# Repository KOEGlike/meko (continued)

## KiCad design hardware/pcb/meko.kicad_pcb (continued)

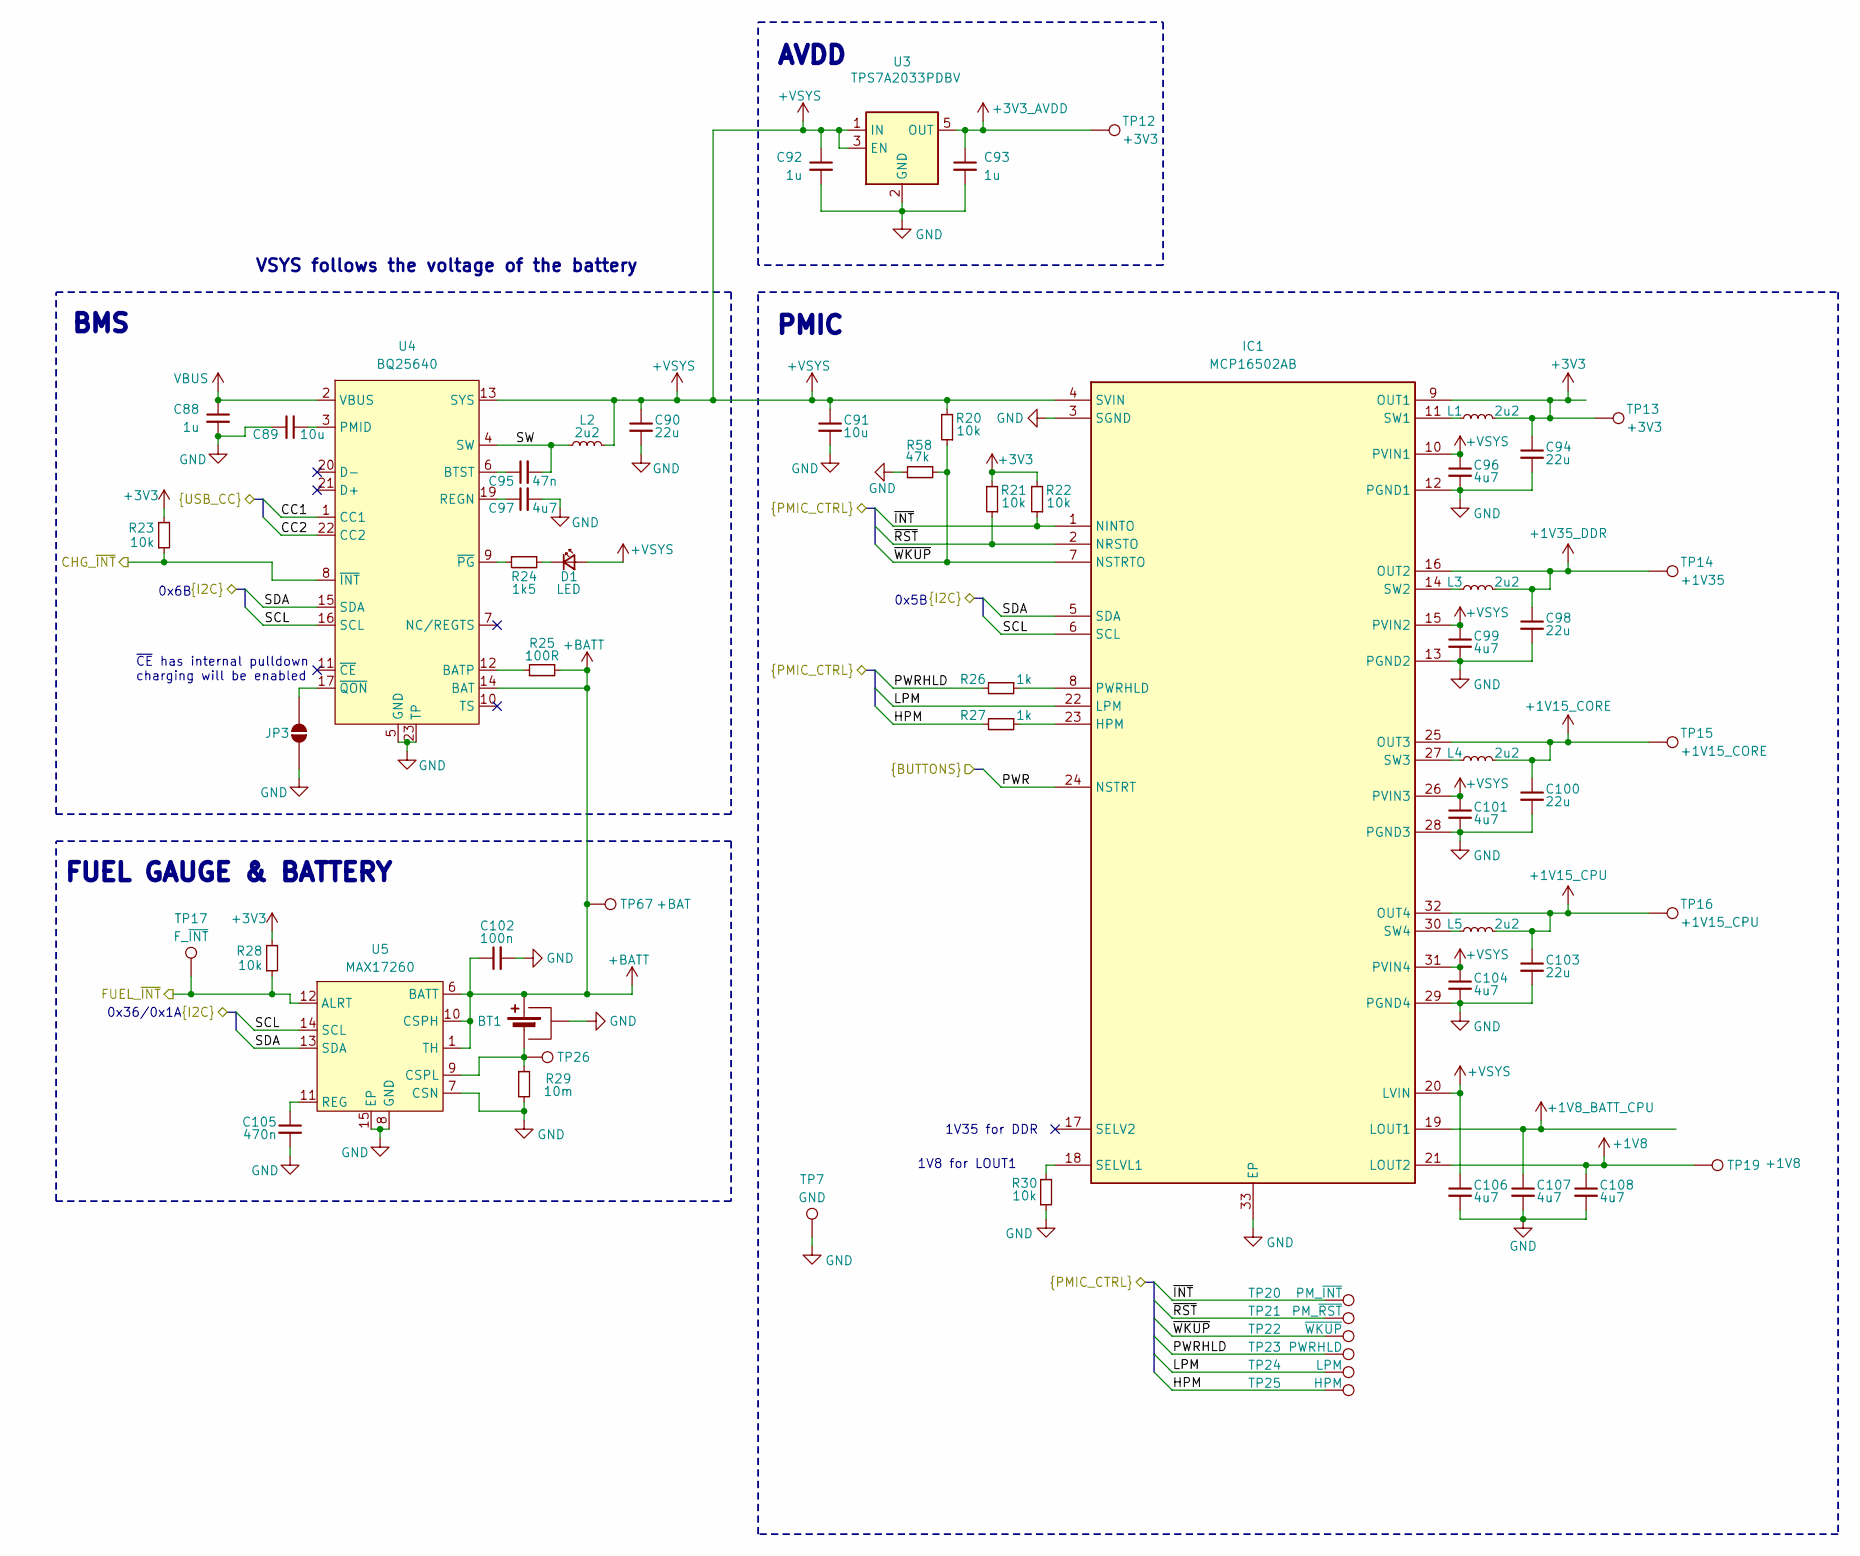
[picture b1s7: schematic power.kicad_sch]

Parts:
BT1: Battery_Cell; JST_GH_SM02B-GHS-TB_1x02-1MP_P1.25mm_Horizontal; MPN SM02B-GHS-TB(LF)(SN); LCSC C189893
C88, C92, C93: 1u; C_0402_1005Metric
C89, C91: 10u; C_0402_1005Metric
C90, C94, C98, C100, C103: 22u; C_0603_1608Metric
C95: 47n; C_0201_0603Metric
C96, C97, C99, C101, C104, C106, C107, C108: 4u7; C_0402_1005Metric
C102: 100n; C_0201_0603Metric
C105: 470n; C_0201_0603Metric
D1: LED; LED_0603_1608Metric; LCSC C965808
IC1: MCP16502AB; VQFN-32-1EP_5x5mm_P0.5mm_EP3.15x3.15mm; MPN MCP16502AB
JP3: SolderJumper_2_Open; SolderJumper-2_P1.3mm_Open_RoundedPad1.0x1.5mm
L1, L2, L3, L4, L5: 2u2; L_1008_2520Metric; LCSC C391305
R20: 10k; R_0201_0603Metric
R21, R22, R23, R28, R30: 10k; R_0402_1005Metric
R24: 1k5; R_0402_1005Metric
R25: 100R; R_0402_1005Metric
R26, R27: 1k; R_0402_1005Metric
R29: 10m; R_0402_1005Metric
R58: 47k; R_0402_1005Metric
TP7: GND; TestPoint_Pad_D1.0mm
TP12, TP13: +3V3; TestPoint_Pad_D1.0mm
TP14: +1V35; TestPoint_Pad_D1.0mm
TP15: +1V15_CORE; TestPoint_Pad_D1.0mm
TP16: +1V15_CPU; TestPoint_Pad_D1.0mm
TP17: F_~{INT}; TestPoint_Pad_D1.0mm
TP19: +1V8; TestPoint_Pad_D1.0mm
TP20: PM_~{INT}; TestPoint_Pad_D1.0mm
TP21: PM_~{RST}; TestPoint_Pad_D1.0mm
TP22: ~{WKUP}; TestPoint_Pad_D1.0mm
TP23: PWRHLD; TestPoint_Pad_D1.0mm
TP24: LPM; TestPoint_Pad_D1.0mm
TP25, TP26: HPM; TestPoint_Pad_D1.0mm
TP67: +BAT; TestPoint_Pad_D1.0mm
U3: TPS7A2033PDBV; SOT-23-5
U4: BQ25640; VDL0023A-MFG
U5: MAX17260; TDFN-14-1EP_3x3mm_P0.4mm_EP1.78x2.35mm

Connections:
+1V8: C108.1, IC1.21 (LOUT2), TP19.1 (1_1); also elsewhere on the board
+1V8_BATT_CPU: C107.1, IC1.19 (LOUT1); also elsewhere on the board
+1V15_CORE: C100.1, IC1.25 (OUT3), L4.2, TP15.1 (1_1); also elsewhere on the board
+1V15_CPU: C103.1, IC1.32 (OUT4), L5.2, TP16.1 (1_1); also elsewhere on the board
+1V35_DDR: C98.1, IC1.16 (OUT2), L3.2, TP14.1 (1_1); also elsewhere on the board
+3V3: C94.1, IC1.9 (OUT1), L1.2, R21.2, R22.2, R23.2, R28.2, TP13.1 (1_1); also elsewhere on the board
+3V3_AVDD: C93.1, TP12.1 (1_1), U3.5 (OUT); also elsewhere on the board
+BATT: BT1.1 (+), C102.1, R25.2, TP67.1 (1_1), U4.14 (BAT), U5.1 (TH), U5.6 (BATT), U5.10 (CSPH)
+VSYS: C90.1, C91.1, C92.1, C96.1, C99.1, C101.1, C104.1, C106.1, D1.2 (A), IC1.4 (SVIN), IC1.10 (PVIN1), IC1.15 (PVIN2), IC1.20 (LVIN), IC1.26 (PVIN3), IC1.31 (PVIN4), L2.2, R20.2, U3.1 (IN), U3.3 (EN), U4.13 (SYS)
/Audio/SCL: IC1.6 (SCL), U4.16 (SCL), U5.14 (SCL); also elsewhere on the board
/Audio/SDA: IC1.5 (SDA), U4.15 (SDA), U5.13 (SDA); also elsewhere on the board
/Buttons/PWR: IC1.24 (NSTRT); also elsewhere on the board
/Power/CC1: U4.1 (CC1); also elsewhere on the board
/Power/CC2: U4.22 (CC2); also elsewhere on the board
/Power/CHG_~INT: R23.1, U4.8 (~INT); also elsewhere on the board
/Power/FUEL_~INT: R28.1, TP17.1 (1_1), U5.12 (ALRT); also elsewhere on the board
/Power/HPM: R27.2, TP25.1 (1_1); also elsewhere on the board
/Power/LPM: IC1.22 (LPM), TP24.1 (1_1); also elsewhere on the board
/Power/PWRHLD: R26.2, TP23.1 (1_1); also elsewhere on the board
/Power/SW: C95.2, L2.1, U4.4 (SW)
/Power/~INT: IC1.1 (NINTO), R22.1, TP20.1 (1_1); also elsewhere on the board
/Power/~RST: IC1.2 (NRSTO), R21.1, TP21.1 (1_1); also elsewhere on the board
/Power/~WKUP: IC1.7 (NSTRTO), R20.1, R58.2, TP22.1 (1_1); also elsewhere on the board
GND: BT1.MP, C88.2, C89.2, C90.2, C91.2, C92.2, C93.2, C94.2, C96.2, C97.2, C98.2, C99.2, C100.2, C101.2, C102.2, C103.2, C104.2, C105.2, C106.2, C107.2, C108.2, IC1.3 (SGND), IC1.12 (PGND1), IC1.13 (PGND2), IC1.28 (PGND3), IC1.29 (PGND4), IC1.33 (EP), JP3.1 (A), R29.2, R30.1, R58.1, TP7.1 (1_1), U3.2 (GND), U4.5 (GND), U4.18 (GND), U4.23 (TP), U5.7 (CSN), U5.8 (GND), U5.15 (EP); also elsewhere on the board
unnamed: BT1.2 (-), R29.1, TP26.1 (1_1), U5.9 (CSPL)
unnamed: D1.1 (K), R24.2
unnamed: IC1.23 (HPM), R27.1
unnamed: IC1.8 (PWRHLD), R26.1
unnamed: IC1.18 (SELVL1), R30.2
unnamed: IC1.11 (SW1), L1.1
unnamed: IC1.14 (SW2), L3.1
unnamed: IC1.27 (SW3), L4.1
unnamed: IC1.30 (SW4), L5.1
unnamed: JP3.2 (B), U4.17 (~QON)
unnamed: R25.1, U4.12 (BATP)
unnamed: C95.1, U4.6 (BTST)
unnamed: C89.1, U4.3 (PMID)
unnamed: C97.1, U4.19 (REGN)
unnamed: R24.1, U4.9 (~PG)
unnamed: C105.1, U5.11 (REG)
VBUS: C88.1, U4.2 (VBUS); also elsewhere on the board

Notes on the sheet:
0x5B
0x6B
VSYS follows the voltage of the battery
0x36/0x1A
1V35 for DDR
PMIC
BMS
AVDD
1V8 for LOUT1
~{CE} has internal pulldown charging will be enabled
FUEL GAUGE & BATTERY

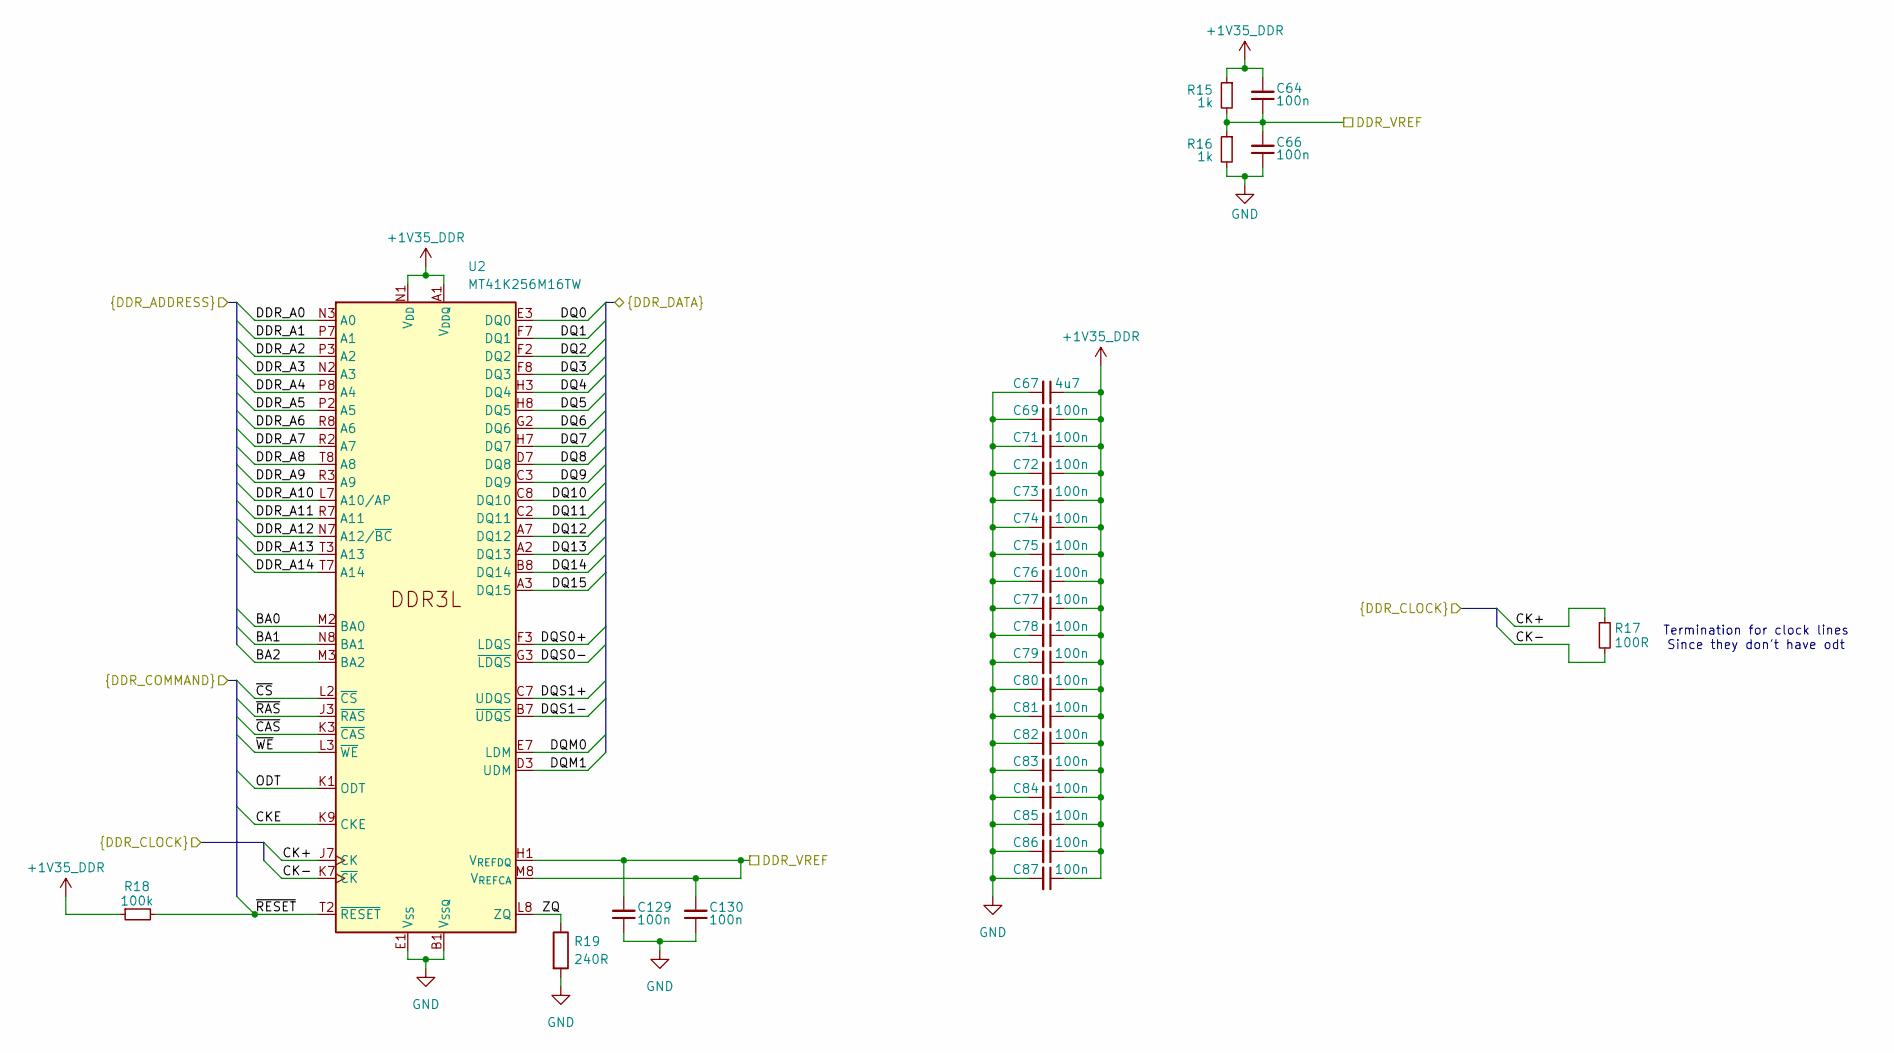
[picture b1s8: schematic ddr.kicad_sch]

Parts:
C64, C66, C69, C71, C72, C73, C74, C76, C77, C78, C79, C80, C81, C82, C83, C84, C85, C86, C87, C129, C130: 100n; C_0201_0603Metric
C67: 4u7; C_0402_1005Metric
C75: 100n; C_0201_0603Metric_Dense
R15, R16: 1k; R_0201_0603Metric
R17: 100R; R_0201_0603Metric
R18: 100k; R_0201_0603Metric
R19: 240R; R_0201_0603Metric
U2: MT41K256M16TW; Micron_FBGA-96_8x14mm_Layout9x16_P0.8mm; LCSC C253882

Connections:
+1V35_DDR: C64.2, C67.1, C69.1, C71.1, C72.1, C73.1, C74.1, C75.1, C76.1, C77.1, C78.1, C79.1, C80.1, C81.1, C82.1, C83.1, C84.1, C85.1, C86.1, C87.1, R15.1, R18.1, U2.A1 (V_{DDQ}), U2.A8 (V_{DDQ}), U2.B2 (V_{DD}), U2.C1 (V_{DDQ}), U2.C9 (V_{DDQ}), U2.D2 (V_{DDQ}), U2.D9 (V_{DD}), U2.E9 (V_{DDQ}), U2.F1 (V_{DDQ}), U2.G7 (V_{DD}), U2.H2 (V_{DDQ}), U2.H9 (V_{DDQ}), U2.K2 (V_{DD}), U2.K8 (V_{DD}), U2.N1 (V_{DD}), U2.N9 (V_{DD}), U2.R1 (V_{DD}), U2.R9 (V_{DD}); also elsewhere on the board
/DDR/BA0: U2.M2 (BA0); also elsewhere on the board
/DDR/BA1: U2.N8 (BA1); also elsewhere on the board
/DDR/BA2: U2.M3 (BA2); also elsewhere on the board
/DDR/CK+: R17.1, U2.J7 (CK); also elsewhere on the board
/DDR/CK-: R17.2, U2.K7 (~CK); also elsewhere on the board
/DDR/CKE: U2.K9 (CKE); also elsewhere on the board
/DDR/DDR_A0: U2.N3 (A0); also elsewhere on the board
/DDR/DDR_A1: U2.P7 (A1); also elsewhere on the board
/DDR/DDR_A2: U2.P3 (A2); also elsewhere on the board
/DDR/DDR_A3: U2.N2 (A3); also elsewhere on the board
/DDR/DDR_A4: U2.P8 (A4); also elsewhere on the board
/DDR/DDR_A5: U2.P2 (A5); also elsewhere on the board
/DDR/DDR_A6: U2.R8 (A6); also elsewhere on the board
/DDR/DDR_A7: U2.R2 (A7); also elsewhere on the board
/DDR/DDR_A8: U2.T8 (A8); also elsewhere on the board
/DDR/DDR_A9: U2.R3 (A9); also elsewhere on the board
/DDR/DDR_A10: U2.L7 (A10/AP); also elsewhere on the board
/DDR/DDR_A11: U2.R7 (A11); also elsewhere on the board
/DDR/DDR_A12: U2.N7 (A12/~BC); also elsewhere on the board
/DDR/DDR_A13: U2.T3 (A13); also elsewhere on the board
/DDR/DDR_A14: U2.T7 (A14); also elsewhere on the board
/DDR/DDR_VREF: C64.1, C66.2, C129.2, C130.2, R15.2, R16.1, U2.H1 (V_{REFDQ}), U2.M8 (V_{REFCA}); also elsewhere on the board
/DDR/DQ0: U2.E3 (DQ0); also elsewhere on the board
/DDR/DQ1: U2.F7 (DQ1); also elsewhere on the board
/DDR/DQ2: U2.F2 (DQ2); also elsewhere on the board
/DDR/DQ3: U2.F8 (DQ3); also elsewhere on the board
/DDR/DQ4: U2.H3 (DQ4); also elsewhere on the board
/DDR/DQ5: U2.H8 (DQ5); also elsewhere on the board
/DDR/DQ6: U2.G2 (DQ6); also elsewhere on the board
/DDR/DQ7: U2.H7 (DQ7); also elsewhere on the board
/DDR/DQ8: U2.D7 (DQ8); also elsewhere on the board
/DDR/DQ9: U2.C3 (DQ9); also elsewhere on the board
/DDR/DQ10: U2.C8 (DQ10); also elsewhere on the board
/DDR/DQ11: U2.C2 (DQ11); also elsewhere on the board
/DDR/DQ12: U2.A7 (DQ12); also elsewhere on the board
/DDR/DQ13: U2.A2 (DQ13); also elsewhere on the board
/DDR/DQ14: U2.B8 (DQ14); also elsewhere on the board
/DDR/DQ15: U2.A3 (DQ15); also elsewhere on the board
/DDR/DQM0: U2.E7 (LDM); also elsewhere on the board
/DDR/DQM1: U2.D3 (UDM); also elsewhere on the board
/DDR/DQS0+: U2.F3 (LDQS); also elsewhere on the board
/DDR/DQS0-: U2.G3 (~LDQS); also elsewhere on the board
/DDR/DQS1+: U2.C7 (UDQS); also elsewhere on the board
/DDR/DQS1-: U2.B7 (~UDQS); also elsewhere on the board
/DDR/ODT: U2.K1 (ODT); also elsewhere on the board
/DDR/ZQ: R19.1, U2.L8 (ZQ)
/DDR/~CAS: U2.K3 (~CAS); also elsewhere on the board
/DDR/~CS: U2.L2 (~CS); also elsewhere on the board
/DDR/~RAS: U2.J3 (~RAS); also elsewhere on the board
/DDR/~RESET: R18.2, U2.T2 (~RESET); also elsewhere on the board
/DDR/~WE: U2.L3 (~WE); also elsewhere on the board
GND: C66.1, C67.2, C69.2, C71.2, C72.2, C73.2, C74.2, C75.2, C76.2, C77.2, C78.2, C79.2, C80.2, C81.2, C82.2, C83.2, C84.2, C85.2, C86.2, C87.2, C129.1, C130.1, R16.2, R19.2, U2.A9 (V_{SS}), U2.B1 (V_{SSQ}), U2.B3 (V_{SS}), U2.B9 (V_{SSQ}), U2.D1 (V_{SSQ}), U2.D8 (V_{SSQ}), U2.E1 (V_{SS}), U2.E2 (V_{SSQ}), U2.E8 (V_{SSQ}), U2.F9 (V_{SSQ}), U2.G1 (V_{SSQ}), U2.G8 (V_{SS}), U2.G9 (V_{SSQ}), U2.J2 (V_{SS}), U2.J8 (V_{SS}), U2.M1 (V_{SS}), U2.M9 (V_{SS}), U2.P1 (V_{SS}), U2.P9 (V_{SS}), U2.T1 (V_{SS}), U2.T9 (V_{SS}); also elsewhere on the board

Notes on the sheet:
Termination for clock lines Since they don't have odt

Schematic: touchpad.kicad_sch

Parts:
C124, C125: 1u; C_0402_1005Metric
J9: 503480-0540; MPN 5034800540; LCSC C5527934
R57: 10k; R_0402_1005Metric
TP62: T_~{INT}; TestPoint_Pad_D1.0mm
TP63: HAPT+; TestPoint_Pad_D2.0mm
TP64: HAPT-; TestPoint_Pad_D2.0mm
TP65: HAPT_EN; TestPoint_Pad_D1.0mm
U7: DRV2605LDGS; TSSOP-10_3x3mm_P0.5mm

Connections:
+3V3: C124.2, J9.1, R57.2, U7.6 (VDD/NC), U7.10 (VDD); also elsewhere on the board
/Audio/SCL: U7.2 (SCL); also elsewhere on the board
/Audio/SDA: U7.3 (SDA); also elsewhere on the board
/SAMA7/HAPT_EN: TP65.1 (1_1), U7.5 (EN); also elsewhere on the board
/SAMA7/TOUCH.SCL: J9.5; also elsewhere on the board
/SAMA7/TOUCH.SDA: J9.3; also elsewhere on the board
/SAMA7/TOUCH_~INT: J9.2, R57.1, TP62.1 (1_1); also elsewhere on the board
/Touchpad/HAPT+: TP63.1 (1_1), U7.7 (OUT+)
/Touchpad/HAPT-: TP64.1 (1_1), U7.9 (OUT-)
GND: C124.1, C125.1, J9.4, J9.MP_1, J9.MP_2, U7.4 (IN/TRIG), U7.8 (GND); also elsewhere on the board
unnamed: C125.2, U7.1 (REG)

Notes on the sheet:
TOUCHPAD CONN
HAPTIC

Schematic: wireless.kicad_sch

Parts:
C109, C110: 1u; C_0402_1005Metric
C111, C112: 9p; C_0201_0603Metric
IC2: MAYA-W386-00B; MPN MAYA-W383-00B
R31, R32, R38, R39: 10k; R_0402_1005Metric
R33, R34, R35, R36, R37: 47k; R_0402_1005Metric
TP28: BT_EN; TestPoint_Pad_D1.0mm
TP29: RF_RX; TestPoint_Pad_D1.0mm
TP30: RF_TX; TestPoint_Pad_D1.0mm
TP31: RF_~{CTS}; TestPoint_Pad_D1.0mm
TP32: RF_~{RTS}; TestPoint_Pad_D1.0mm
TP33: RF_MCLK; TestPoint_Pad_D1.0mm
TP34: RF_BCLK; TestPoint_Pad_D1.0mm
TP35: RF_FSYNC; TestPoint_Pad_D1.0mm
TP36: RF_DOUT; TestPoint_Pad_D1.0mm
TP37: RF_DIN; TestPoint_Pad_D1.0mm
TP40: WL_EN; TestPoint_Pad_D1.0mm
TP41: RF_CK; TestPoint_Pad_D1.0mm
TP42: RF_CMD; TestPoint_Pad_D1.0mm
TP43: RF_DAT0; TestPoint_Pad_D1.0mm
TP44: RF_DAT1; TestPoint_Pad_D1.0mm
TP45: RF_DAT2; TestPoint_Pad_D1.0mm
TP46: RF_DAT3; TestPoint_Pad_D1.0mm
Y3: 32kHz768; Crystal_SMD_MicroCrystal_CC7V-T1A-2Pin_3.2x1.5mm; MPN SC-32S32.768kHz20PPM7pF

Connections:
+1V8: C109.2, IC2.A2 (1V8); also elsewhere on the board
+3V3: C110.1, IC2.A7 (3V3), IC2.B7 (3V3), R33.1, R34.1, R35.1, R36.1, R37.1; also elsewhere on the board
/SAMA7/BT.BCLK: IC2.D8 (PCM_CLK), TP34.1 (1_1); also elsewhere on the board
/SAMA7/BT.DEV_WAKE: IC2.J9 (BT_DEV_WAKE), R31.2; also elsewhere on the board
/SAMA7/BT.DIN: IC2.E9 (PCM_DIN), TP37.1 (1_1); also elsewhere on the board
/SAMA7/BT.DOUT: IC2.F9 (PCM_DOUT), TP36.1 (1_1); also elsewhere on the board
/SAMA7/BT.EN: IC2.J7 (BT_EN), TP28.1 (1_1); also elsewhere on the board
/SAMA7/BT.FSYNC: IC2.F8 (PCM_SYNC), TP35.1 (1_1); also elsewhere on the board
/SAMA7/BT.HOST_WAKE: IC2.E7 (BT_HOST_WAKE), R32.2; also elsewhere on the board
/SAMA7/BT.MCLK: IC2.E8 (PCM_MCLK), TP33.1 (1_1); also elsewhere on the board
/SAMA7/BT.RX: IC2.G8 (UART_RX), TP29.1 (1_1); also elsewhere on the board
/SAMA7/BT.TX: IC2.G9 (UART_TX), TP30.1 (1_1); also elsewhere on the board
/SAMA7/BT.~CTS: IC2.H8 (UART_CTSN), TP31.1 (1_1); also elsewhere on the board
/SAMA7/BT.~RTS: IC2.H9 (UART_RTSN), TP32.1 (1_1); also elsewhere on the board
/SAMA7/WIFI.CK: IC2.A4 (SD_CLK), TP41.1 (1_1); also elsewhere on the board
/SAMA7/WIFI.CMD: IC2.B4 (SD_CMD), R33.2, TP42.1 (1_1); also elsewhere on the board
/SAMA7/WIFI.DAT0: IC2.B3 (SD_DAT[0]), R34.2, TP43.1 (1_1); also elsewhere on the board
/SAMA7/WIFI.DAT1: IC2.A3 (SD_DAT[1]), R35.2, TP44.1 (1_1); also elsewhere on the board
/SAMA7/WIFI.DAT2: IC2.B5 (SD_DAT[2]), R36.2, TP45.1 (1_1); also elsewhere on the board
/SAMA7/WIFI.DAT3: IC2.A5 (SD_DAT[3]), R37.2, TP46.1 (1_1); also elsewhere on the board
/SAMA7/WL.DEV_WAKE: IC2.J8 (WL_DEV_WAKE), R39.2; also elsewhere on the board
/SAMA7/WL.EN: IC2.J3 (WL_EN), TP40.1 (1_1); also elsewhere on the board
/SAMA7/WL.HOST_WAKE: IC2.F7 (WL_HOST_WAKE), R38.2; also elsewhere on the board
/Wireless/ANT: IC2.K9 (RF_ANT1), IC2.L9 (ANT_EXT_FEED)
GND: C109.1, C110.2, C111.2, C112.2, IC2.A1 (GND), IC2.A9 (GND), IC2.B2 (GND), IC2.B8 (GND), IC2.E4 (GND), IC2.E5 (GND), IC2.F4 (GND), IC2.F5 (GND), IC2.H4 (GND), IC2.H5 (GND), IC2.H7 (JTAG_SEL), IC2.K2 (GND), IC2.K3 (GND), IC2.K4 (GND), IC2.K5 (GND), IC2.K6 (GND), IC2.K7 (GND), IC2.K8 (GND), IC2.L1 (GND), IC2.M1 (GND), IC2.M2 (GND), IC2.M8 (GND), IC2.M9 (GND), R31.1, R32.1, R38.1, R39.1; also elsewhere on the board
unnamed: C112.1, IC2.C2 (SLP_XTAL_IN), Y3.1
unnamed: C111.1, IC2.D2 (SLP_XTAL_OUT), Y3.2

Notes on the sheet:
WL EN has internal pull down
Mic input, and digital outputs
RF Switch Control Lines
BT EN has internal pull down
External Memory/Flash
Connecting the output to the integrated PCB antenna
JTAG Pins

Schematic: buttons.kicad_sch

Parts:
C126: 100n; C_0201_0603Metric
R56: 10k; R_0402_1005Metric
SW1, SW2, SW3, SW4, SW5: SW_Push_Shielded; SW_Push_1P1T-MP_NO_Horizontal_Alps_SKRTLAE010; MPN SKRTLAE010; LCSC C110293

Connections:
/Buttons/PWR: C126.2, R56.2; also elsewhere on the board
/Buttons/SIDE_L: SW4.2; also elsewhere on the board
/Buttons/SIDE_R: SW5.2; also elsewhere on the board
/Buttons/VOL+: SW2.2; also elsewhere on the board
/Buttons/VOL-: SW3.2; also elsewhere on the board
GND: C126.1, SW1.1, SW1.MP (B), SW2.1, SW2.MP (B), SW3.1, SW3.MP (B), SW4.1, SW4.MP (B), SW5.1, SW5.MP (B); also elsewhere on the board
unnamed: R56.1, SW1.2

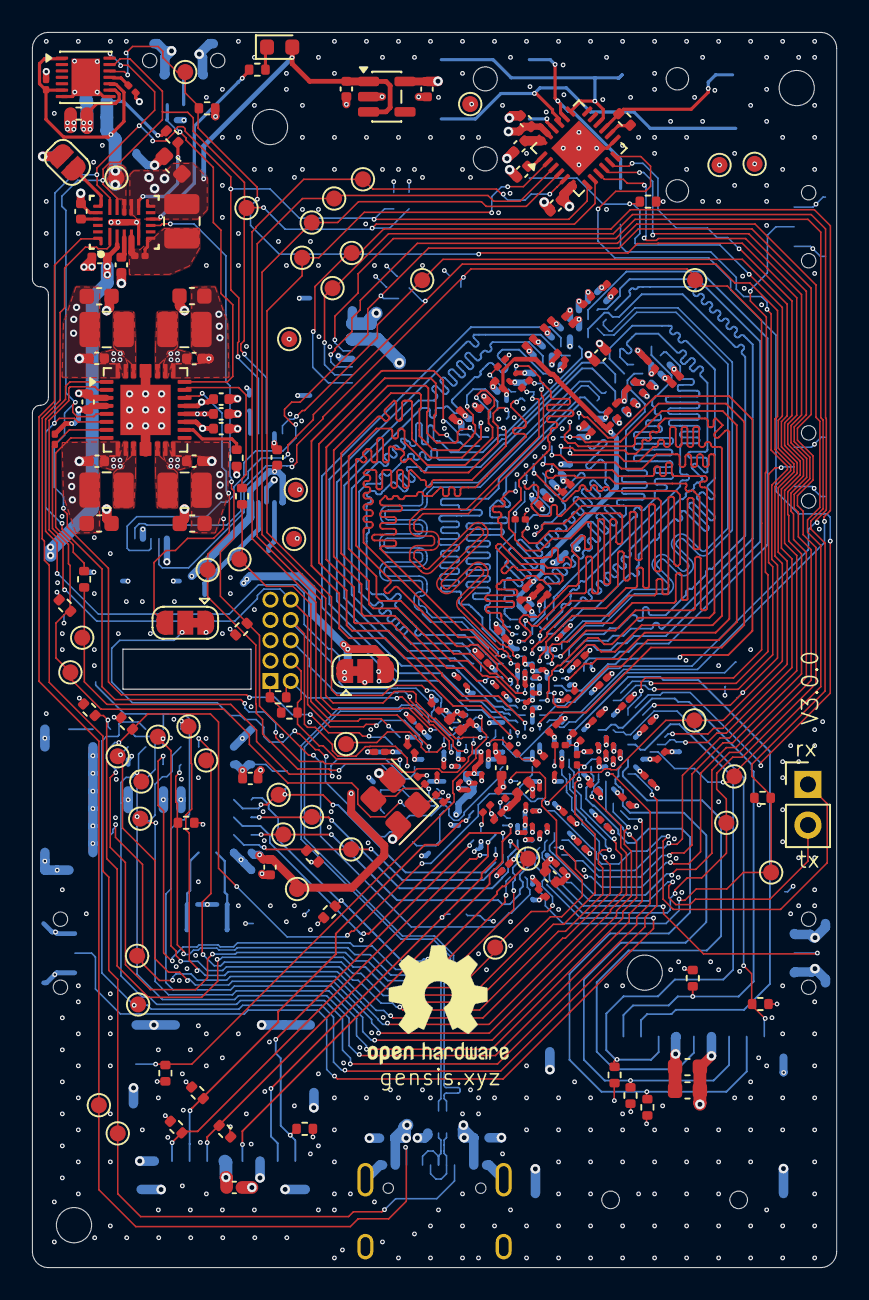
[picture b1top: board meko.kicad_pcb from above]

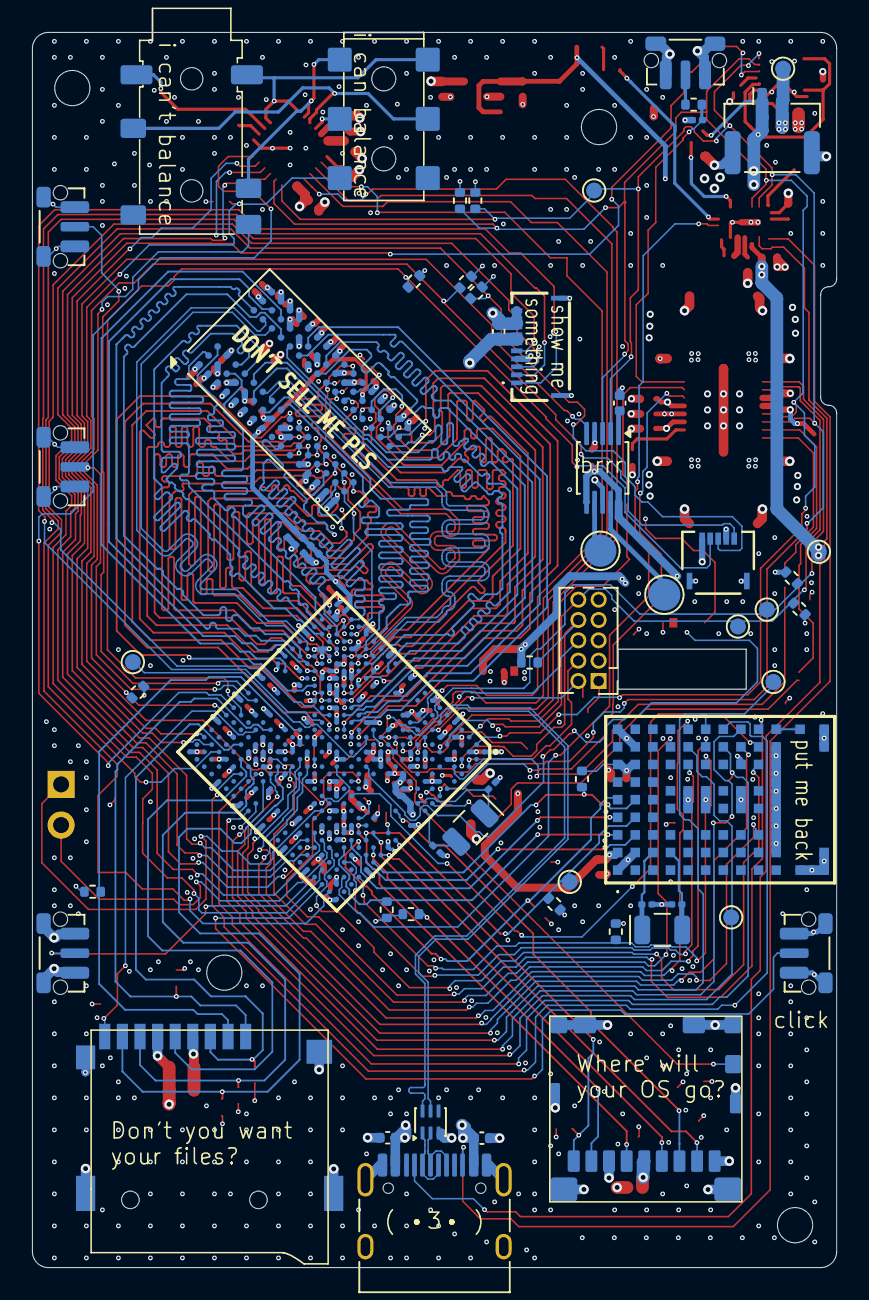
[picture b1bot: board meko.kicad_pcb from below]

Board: 6 copper layers, 50.2 x 77.2 mm, 275 parts (61 on the bottom side), 189 nets.

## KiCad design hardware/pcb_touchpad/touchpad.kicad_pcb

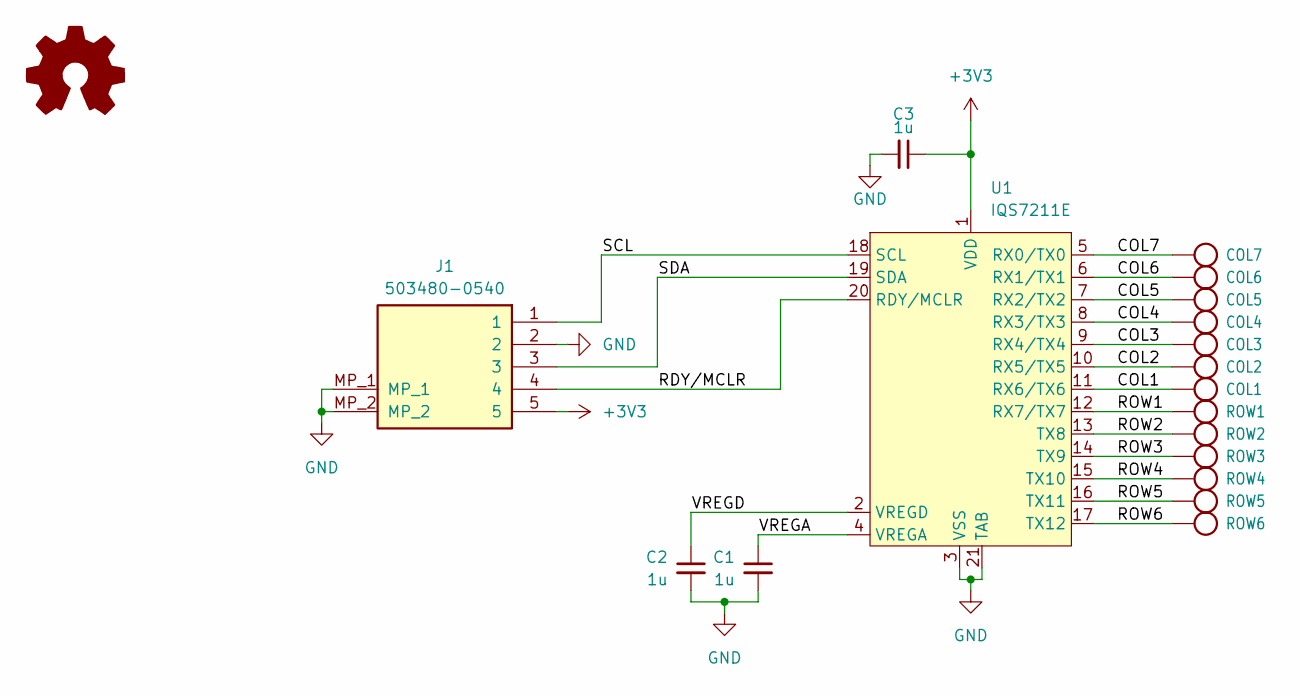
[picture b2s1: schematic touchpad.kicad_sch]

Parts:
C1, C2, C3: 1u; C_0402_1005Metric
COL1, COL2, COL3, COL4, COL5, COL6, COL7: TESTPOINTPAD_0_5MM; PAD_0_5MM
J1: 503480-0540; MPN 5034800540; LCSC C5527934
ROW1, ROW2, ROW3, ROW4, ROW5, ROW6: TESTPOINTPAD_0_5MM; PAD_0_5MM
SYM1: Logo_Open_Hardware_Small; OSHW-Logo2_14.6x12mm_SilkScreen
U1: IQS7211E; QFN-20-1EP_3x3mm_P0.4mm_EP1.65x1.65mm

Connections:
+3V3: C3.1, J1.5, U1.1 (VDD)
/COL1: COL1.P1 (P1_P1), U1.11 (RX6/TX6)
/COL2: COL2.P1 (P1_P1), U1.10 (RX5/TX5)
/COL3: COL3.P1 (P1_P1), U1.9 (RX4/TX4)
/COL4: COL4.P1 (P1_P1), U1.8 (RX3/TX3)
/COL5: COL5.P1 (P1_P1), U1.7 (RX2/TX2)
/COL6: COL6.P1 (P1_P1), U1.6 (RX1/TX1)
/COL7: COL7.P1 (P1_P1), U1.5 (RX0/TX0)
/RDY/MCLR: J1.4, U1.20 (RDY/MCLR)
/ROW1: ROW1.P1 (P1_P1), U1.12 (RX7/TX7)
/ROW2: ROW2.P1 (P1_P1), U1.13 (TX8)
/ROW3: ROW3.P1 (P1_P1), U1.14 (TX9)
/ROW4: ROW4.P1 (P1_P1), U1.15 (TX10)
/ROW5: ROW5.P1 (P1_P1), U1.16 (TX11)
/ROW6: ROW6.P1 (P1_P1), U1.17 (TX12)
/SCL: J1.1, U1.18 (SCL)
/SDA: J1.3, U1.19 (SDA)
/VREGA: C1.1, U1.4 (VREGA)
/VREGD: C2.1, U1.2 (VREGD)
GND: C1.2, C2.2, C3.2, J1.2, J1.MP_1, J1.MP_2, U1.3 (VSS), U1.21 (TAB)

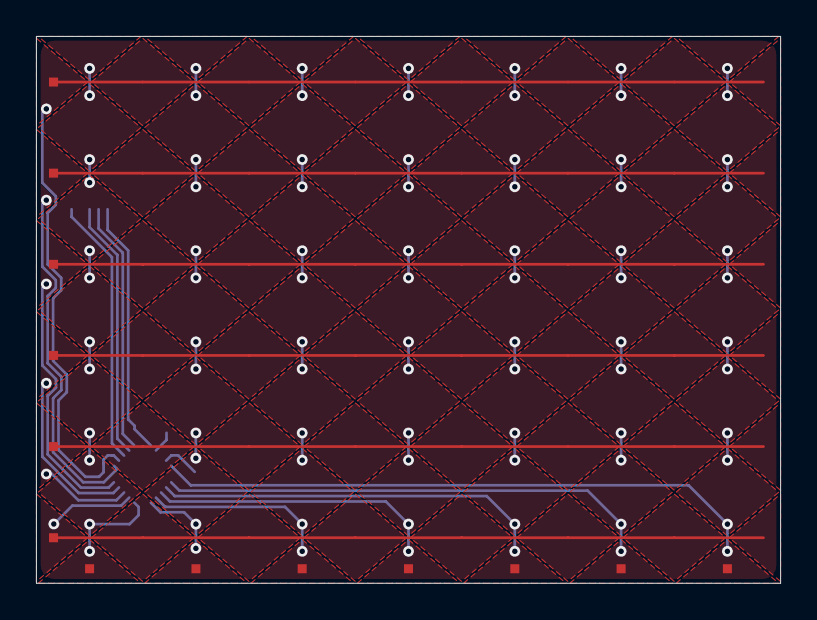
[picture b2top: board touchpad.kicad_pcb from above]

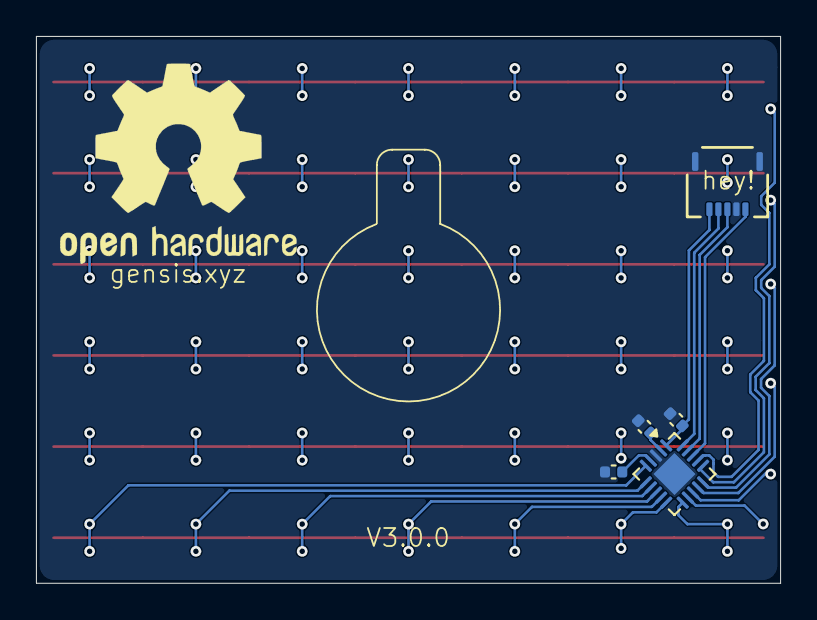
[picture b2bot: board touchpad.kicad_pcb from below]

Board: 2 copper layers, 41.3 x 30.4 mm, 19 parts (6 on the bottom side), 20 nets.
